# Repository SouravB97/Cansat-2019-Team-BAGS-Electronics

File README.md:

# Cansat-2019-Team-BAGS-Electronics
Technical resources pertaining to the cansat created by Team BAGS in June 2019

The cansat contains 3 independant systems.

Section A is responsible for the overall telemetry and processing. It is fitted into the payload and has several I/O devices, including the zigbee radio which communicates with the ground station.

Section B is the camera module. It contains the camera as well as the equipment needed to stabilise it, which ensures that the camera points to one direction with respect to the earth's magnetic field, even if the cansat overall rotates continuosly.

Section C is the container module. It houses the container while the cansat is in the rocket, and releases it at an altitude of 450m as specified in the mission guidelines.

The ground station is reponsible for receiving the telemetry data from the cansat. It uses this data to generate a csv file, sensor data graphs, gps plots, and a tilt animation of the deployed cansat.

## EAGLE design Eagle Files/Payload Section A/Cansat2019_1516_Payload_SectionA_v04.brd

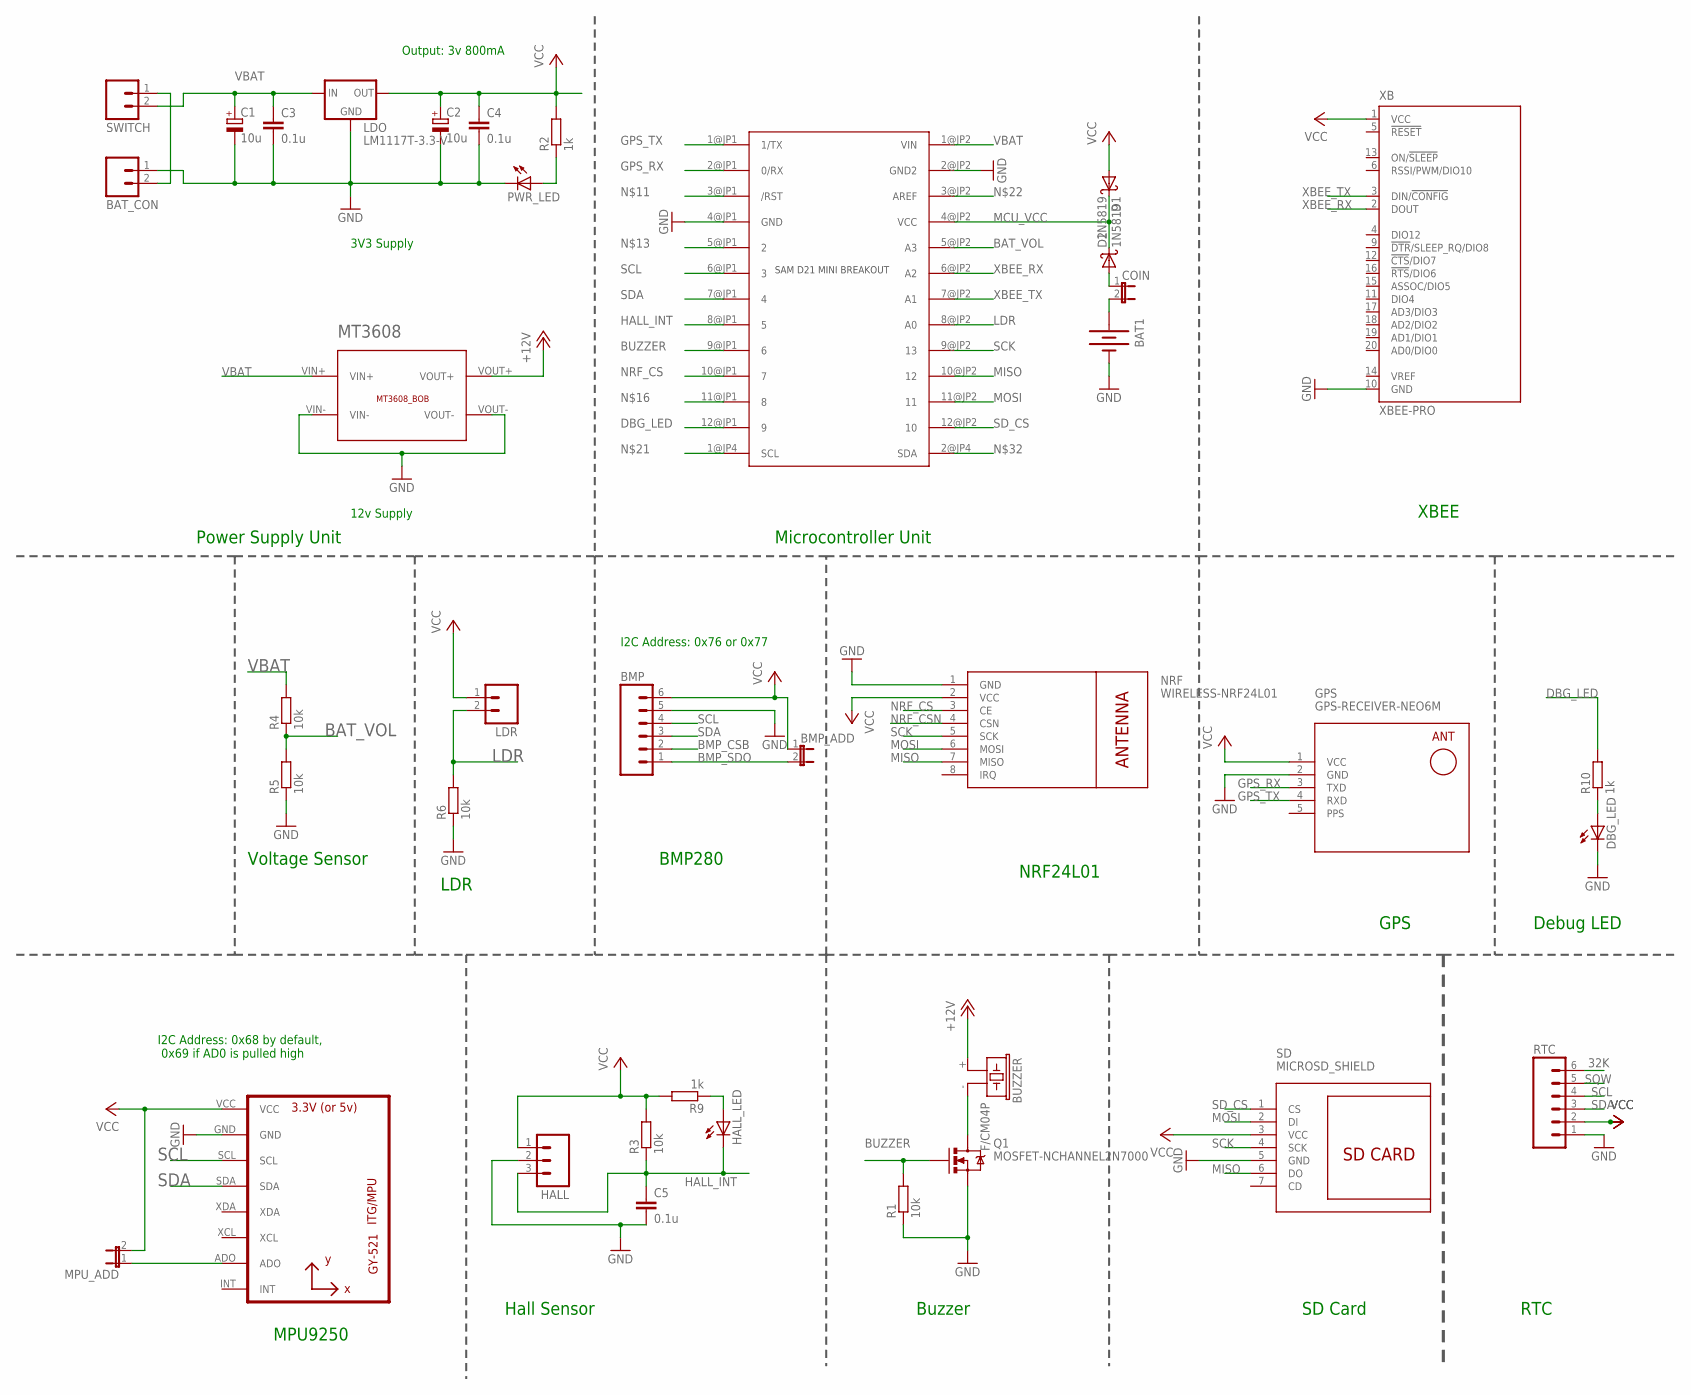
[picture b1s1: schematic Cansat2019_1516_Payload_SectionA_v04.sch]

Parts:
BAT1: BATTERY20PTH; BATTCOM_20MM_PTH
BAT_CON: M02; 02P
BMP: M06; 06P
BMP_ADD: JUMPER-2PTH; 1X02
BUZZER: F/CM04P
C1, C2: 10u; E2,5-6
C3, C4, C5: 0.1u; C025-025X050
COIN: JUMPER-2PTH; 1X02
D1, D2: 1N5819; DO41-10
DBG_LED: LED3MM
GPS: GPS-RECEIVER-NEO6M
HALL: M03; 03P
HALL_LED: LED3MM
LDO: LM1117T-3.3-V; TO220V
LDR: M02; 02P
MPU: GY-521MPU6050; GY-521
MPU_ADD: JUMPER-2PTH; 1X02
MT3608: MT3608_BOB
NRF: WIRELESS-NRF24L01
PWR_LED: LED3MM
Q1: MOSFET-NCHANNEL2N7000; TO-92
R1, R3, R4, R5, R6: 10k; 0204/7
R2, R9, R10: 1k; 0204/7
RTC: M06; 06P
SAMD: SAM_D21_MINI_BREAKOUT; JP1_SPARKFUN-SAMD21-MINI-BREAKOUT-V10
SD: MICROSD_SHIELD
SWITCH: M02; 02P
XB: XBEE-PRO

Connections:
32K: RTC.6
+12V: BUZZER.+ (1), MT3608.VOUT+
BAT_VOL: R4.1, R5.2, SAMD.5@JP2 (A3)
BMP_CSB: BMP.2
BMP_SDO: BMP.1, BMP_ADD.2
BUZZER: Q1.2 (G), R1.2, SAMD.9@JP1 (6)
DBG_LED: R10.2, SAMD.12@JP1 (9)
GND: BAT1.2 (-), BAT_CON.1, BMP.5, C1.-, C2.-, C3.2, C4.2, C5.2, DBG_LED.K (C), GPS.2 (GND), HALL.2, LDO.1 (GND), MPU.GND, MT3608.VIN-, MT3608.VOUT-, NRF.1 (GND), PWR_LED.K (C), Q1.1 (S), R1.1, R5.1, R6.1, RTC.1, SAMD.2@JP2 (GND2), SAMD.4@JP1 (GND), SD.5 (GND), XB.10 (GND)
GPS_RX: GPS.3 (TXD), SAMD.2@JP1 (0/RX)
GPS_TX: GPS.4 (RXD), SAMD.1@JP1 (1/TX)
HALL_INT: C5.1, HALL.3, HALL_LED.K (C), R3.1, SAMD.8@JP1 (5)
LDR: LDR.2, R6.2, SAMD.8@JP2 (A0)
MCU_VCC: D1.C, D2.C, SAMD.4@JP2 (VCC)
MISO: NRF.7 (MISO), SAMD.10@JP2 (12), SD.6 (DO)
MOSI: NRF.6 (MOSI), SAMD.11@JP2 (11), SD.2 (DI)
unnamed: BUZZER.- (2), Q1.3 (D)
unnamed: COIN.1, D2.A
unnamed: PWR_LED.A, R2.1
unnamed: BAT1.1 (+), COIN.2
unnamed: BAT_CON.2, SWITCH.1
unnamed: MPU.ADO, MPU_ADD.1
unnamed: HALL_LED.A, R9.1
unnamed: DBG_LED.A, R10.1
NRF_CS: NRF.3 (CE), SAMD.10@JP1 (7)
NRF_CSN: NRF.4 (CSN)
PPS: GPS.5 (PPS)
SCK: NRF.5 (SCK), SAMD.9@JP2 (13), SD.4 (SCK)
SCL: BMP.4, MPU.SCL, RTC.4, SAMD.6@JP1 (3)
SDA: BMP.3, MPU.SDA, RTC.3, SAMD.7@JP1 (4)
SD_CS: SAMD.12@JP2 (10), SD.1 (CS)
SQW: RTC.5
VBAT: C1.+, C3.1, LDO.3 (IN), MT3608.VIN+, R4.2, SAMD.1@JP2 (VIN), SWITCH.2
VCC: BMP.6, BMP_ADD.1, C2.+, C4.1, D1.A, GPS.1 (VCC), HALL.1, LDO.2 (OUT), LDR.1, MPU.VCC, MPU_ADD.2, NRF.2 (VCC), R2.2, R3.2, R9.2, RTC.2, SD.3 (VCC), XB.1 (VCC)
XBEE_RX: SAMD.6@JP2 (A2), XB.2 (DOUT)
XBEE_TX: SAMD.7@JP2 (A1), XB.3 (DIN/!CONFIG)

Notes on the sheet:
Power Supply Unit
3V3 Supply
12v Supply
Output: 3v 800mA
Microcontroller Unit
Buzzer
Voltage Sensor
BMP280
GPS
XBEE
MPU9250
SD Card
NRF24L01
LDR
Hall Sensor
I2C Address: 0x76 or 0x77
I2C Address: 0x68 by default, 0x69 if AD0 is pulled high
RTC
Debug LED

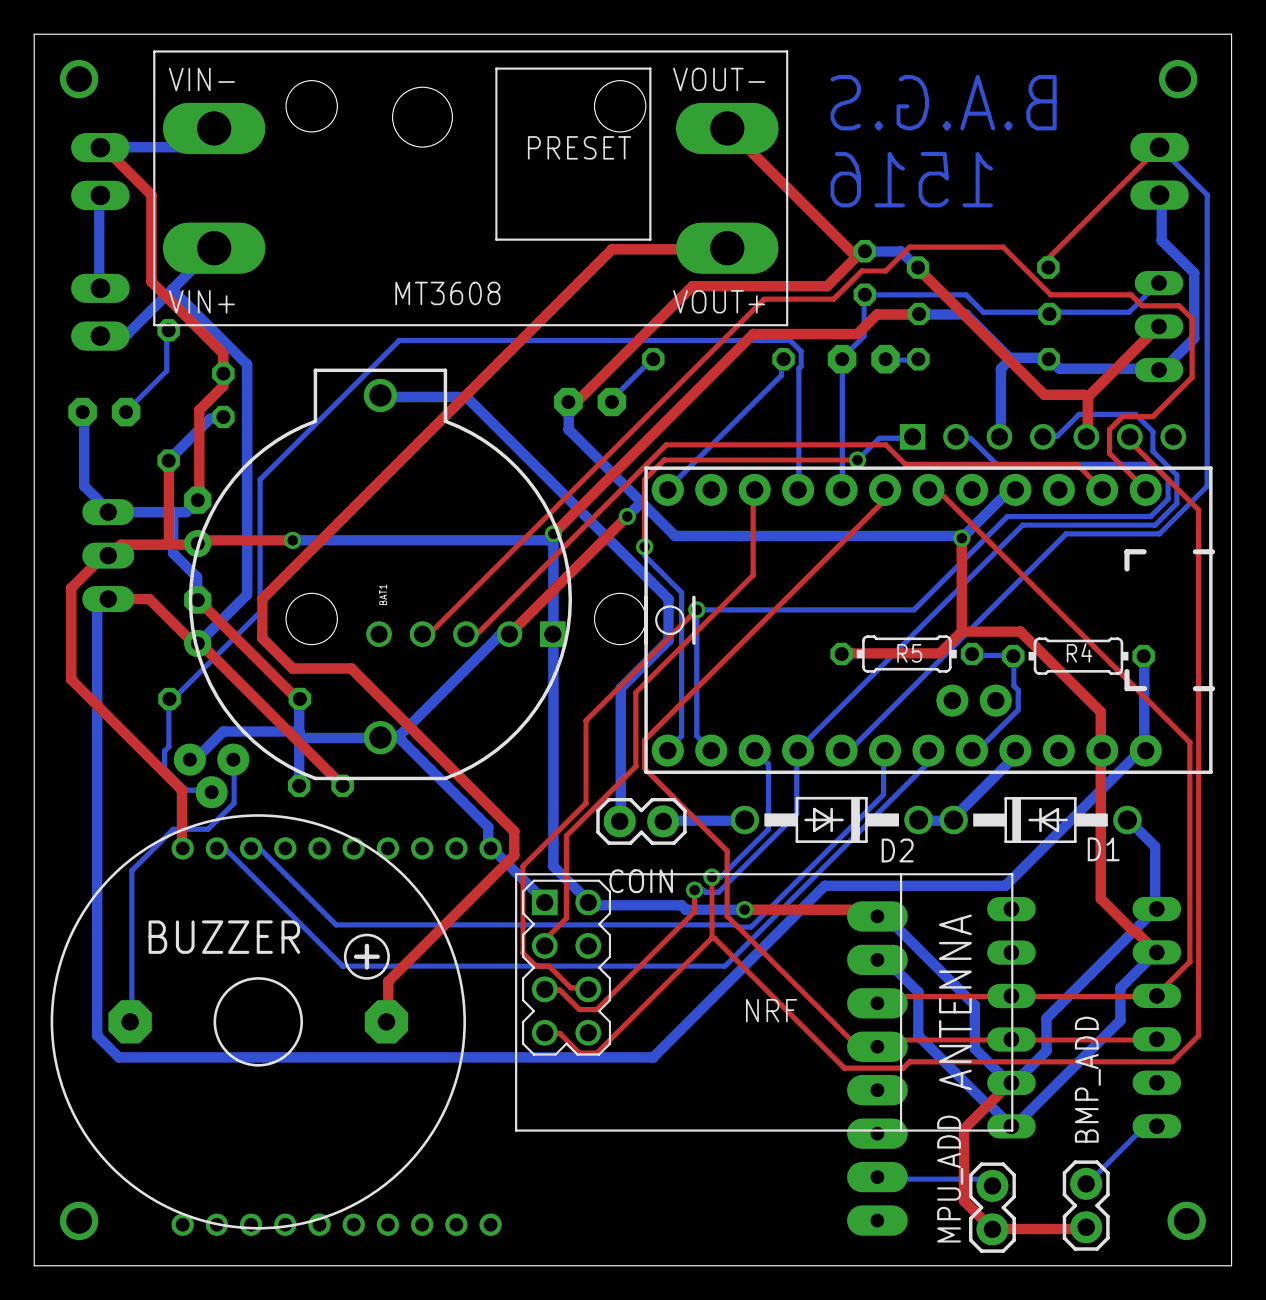
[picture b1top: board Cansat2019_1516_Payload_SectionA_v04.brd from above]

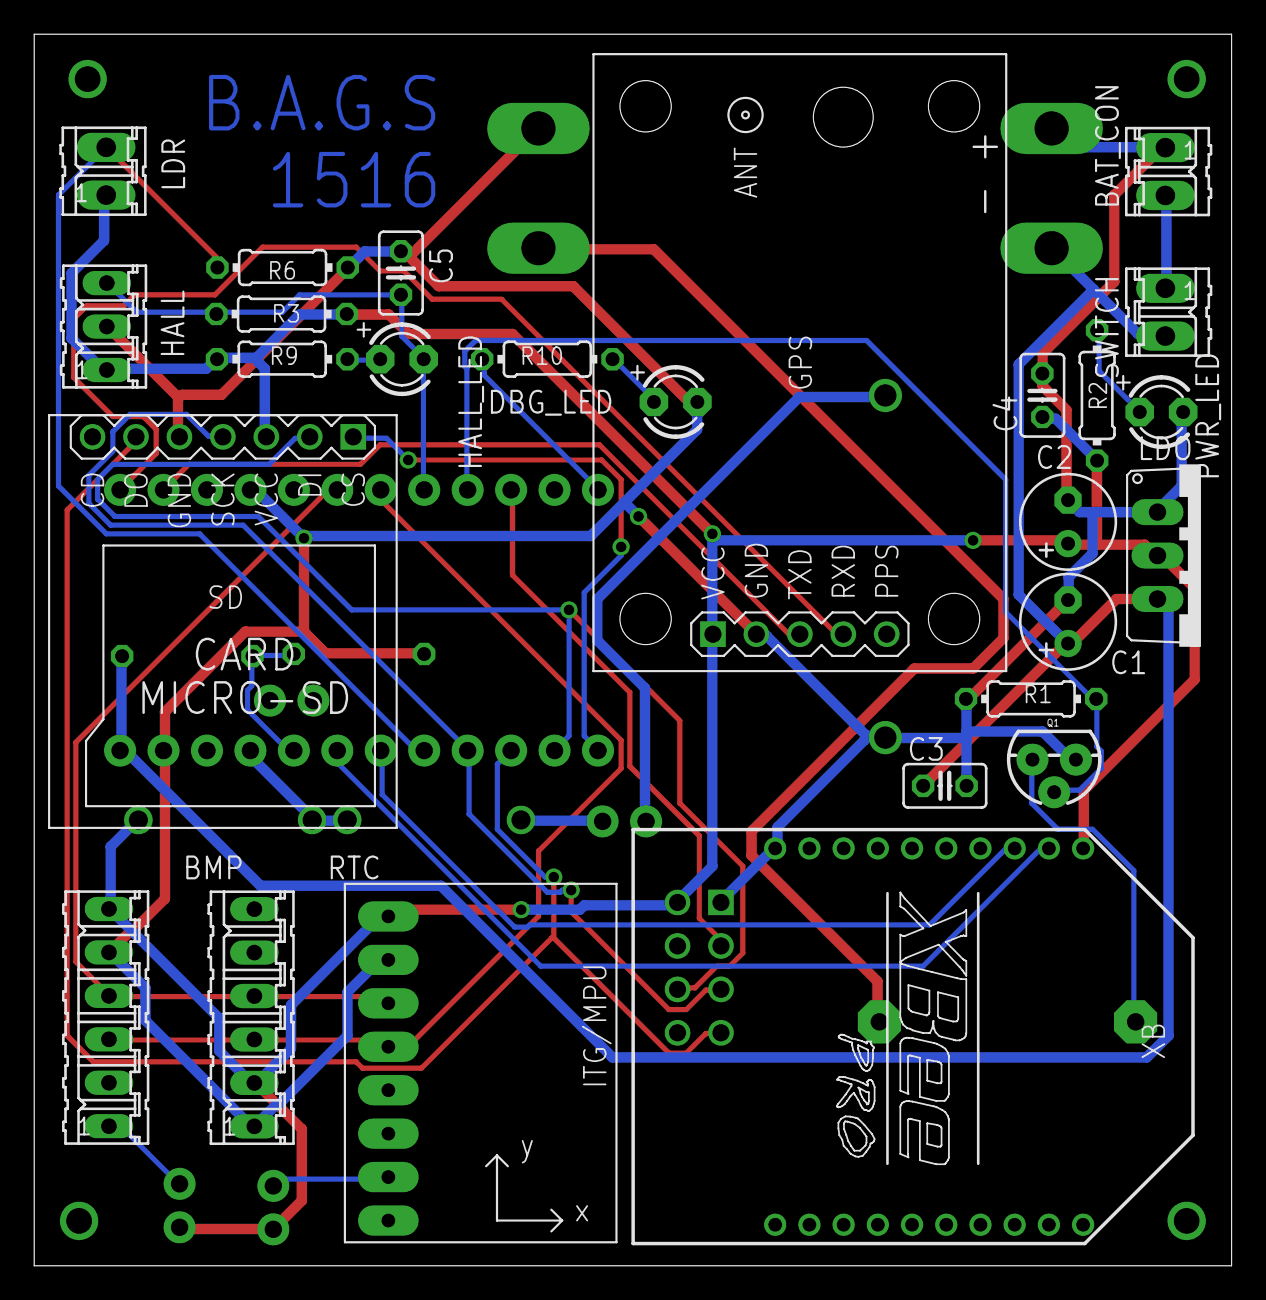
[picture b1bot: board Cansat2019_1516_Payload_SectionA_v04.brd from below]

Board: 2 copper layers, 70.0 x 72.0 mm, 38 parts (26 on the bottom side), 30 nets.

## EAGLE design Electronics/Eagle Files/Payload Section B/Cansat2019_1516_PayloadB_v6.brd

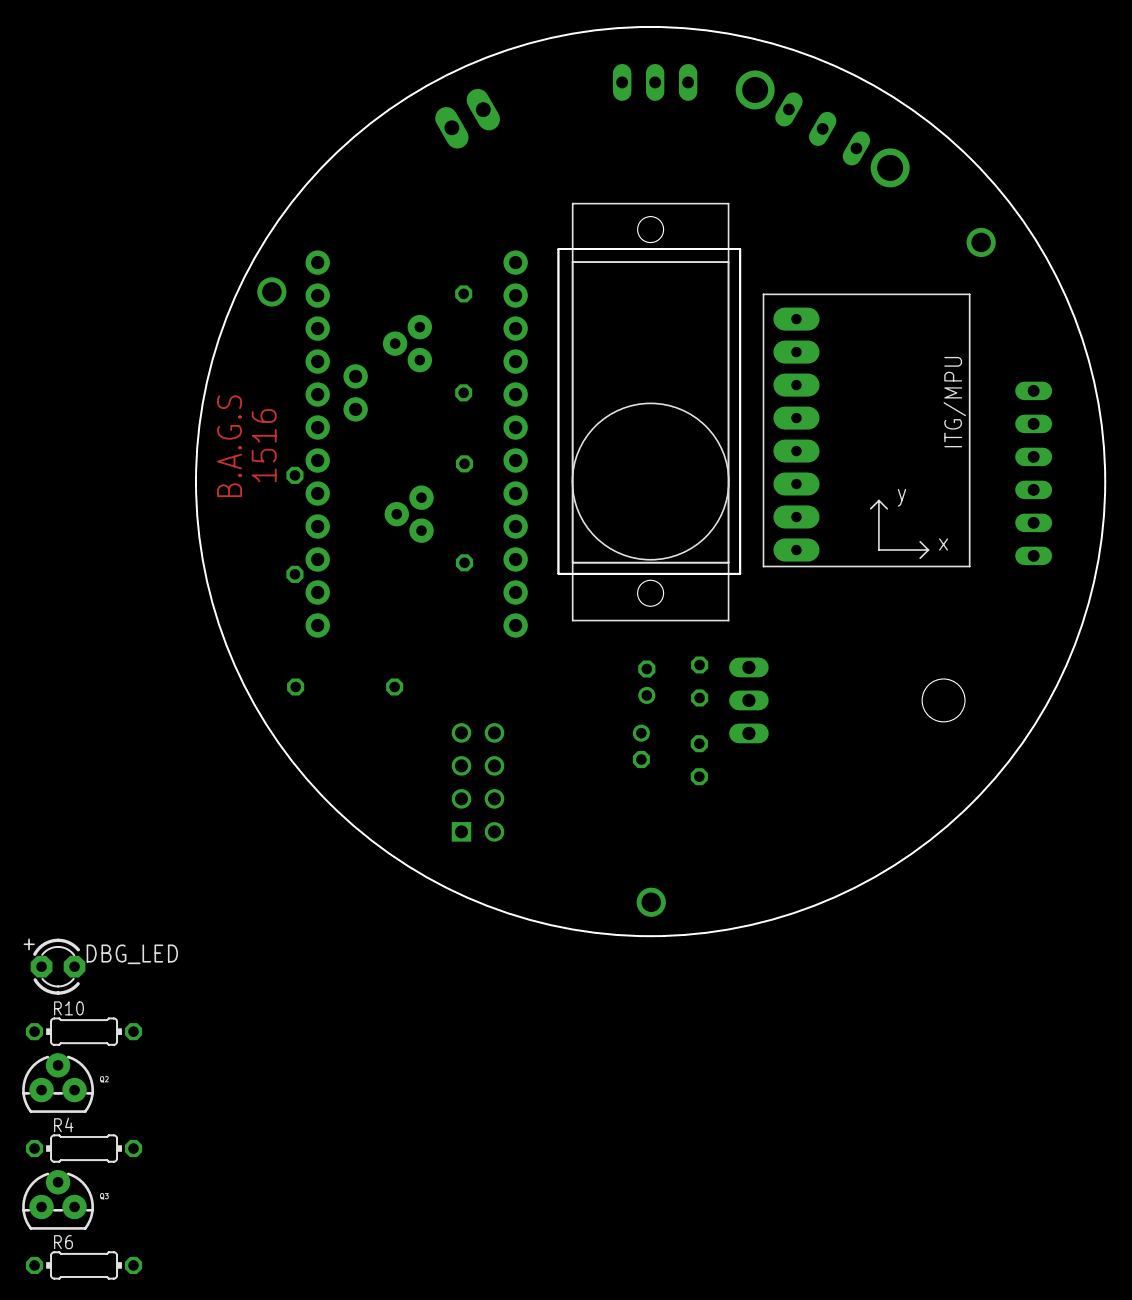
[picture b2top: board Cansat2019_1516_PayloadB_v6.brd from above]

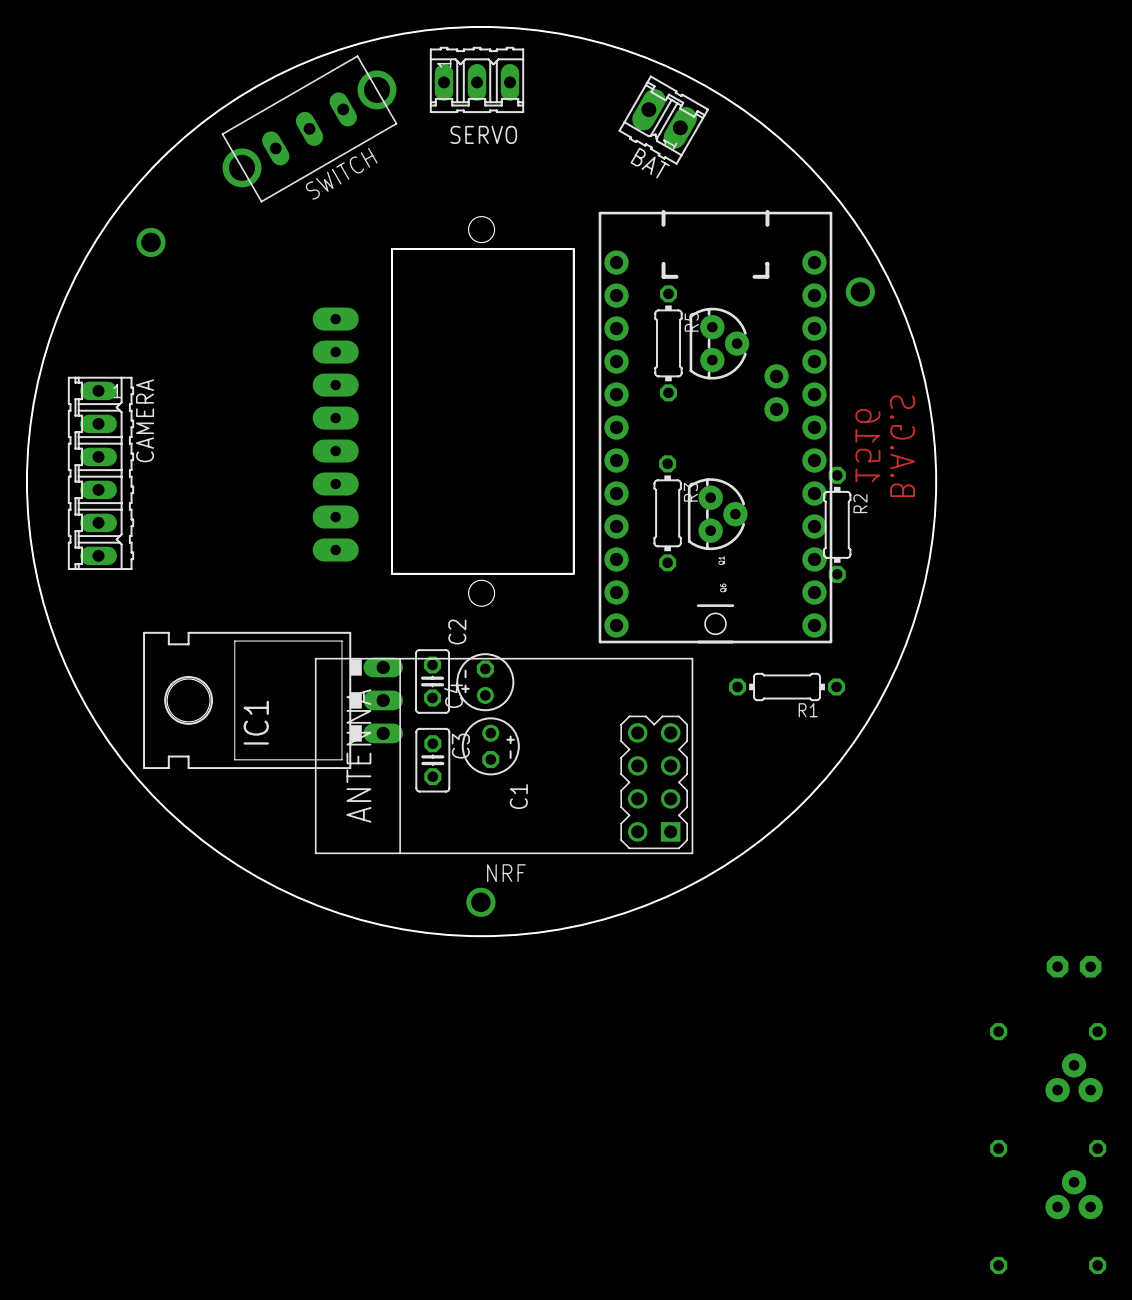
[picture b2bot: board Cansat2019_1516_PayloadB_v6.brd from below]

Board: 2 copper layers, 70.0 x 70.0 mm, 25 parts (17 on the bottom side), 23 nets, no tracks yet.

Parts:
BAT: 02P
C1, C2: 10u; E2-4
C3, C4: 0.1u; C025-025X050
CAMERA: 06P
DBG_LED: LED3MM
IC1: TO-220-ALT
MPU: GY-521MPU6050; GY-521
NRF: WIRELESS-NRF24L01
Q1, Q2, Q3, Q6: MOSFET-NCHANNEL2N7000; TO-92
R1, R2, R3, R4, R5, R6: 10k; 0204/7
R10: 1k; 0204/7
SERVO: 03P
SWITCH: SLIDESWITCH-BIG; BIGSWITCH
U$1: SG90_TOP
U$2: JP1_SPARKFUN-SAMD21-MINI-BREAKOUT-V10

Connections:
!POWER: Q3.2, R6.2
BAT_VOL: R1.1, R2.2, U$2.8@JP2
CE: NRF.3, U$2.11@JP1
CSN: NRF.4, U$2.12@JP2
DBG_LED: R10.2, U$2.12@JP1
GND: BAT.1, C1.-, C2.-, C3.2, C4.2, CAMERA.6, DBG_LED.K, IC1.GND, MPU.GND, NRF.1, Q3.1, Q6.1, R2.1, R3.1, R5.1, R6.1, SERVO.1, U$2.2@JP2, U$2.4@JP1
MISO: NRF.7, U$2.10@JP2
MODE: Q6.2, R5.2, U$2.9@JP1
MODE_O: CAMERA.4, Q6.3
MOSI: NRF.6, U$2.11@JP2
unnamed: BAT.2, SWITCH.3
unnamed: Q2.2, Q3.3, R4.1
unnamed: DBG_LED.A, R10.1
POWER: Q1.2, R3.2, U$2.8@JP1
POWER_OH: CAMERA.2, Q1.3, Q2.3
POWER_OL: CAMERA.3, Q1.1, Q2.1
SCK: NRF.5, U$2.9@JP2
SCL: MPU.SCL, U$2.6@JP1
SDA: MPU.SDA, U$2.7@JP1
SERVO: SERVO.3, U$2.10@JP1
V5: C2.+, C4.1, CAMERA.1, IC1.OUT, R4.2, SERVO.2, U$2.1@JP2
V33: MPU.ADO, MPU.VCC, NRF.2, U$2.4@JP2
VBAT: C1.+, C3.1, IC1.IN, R1.2, SWITCH.1, SWITCH.2

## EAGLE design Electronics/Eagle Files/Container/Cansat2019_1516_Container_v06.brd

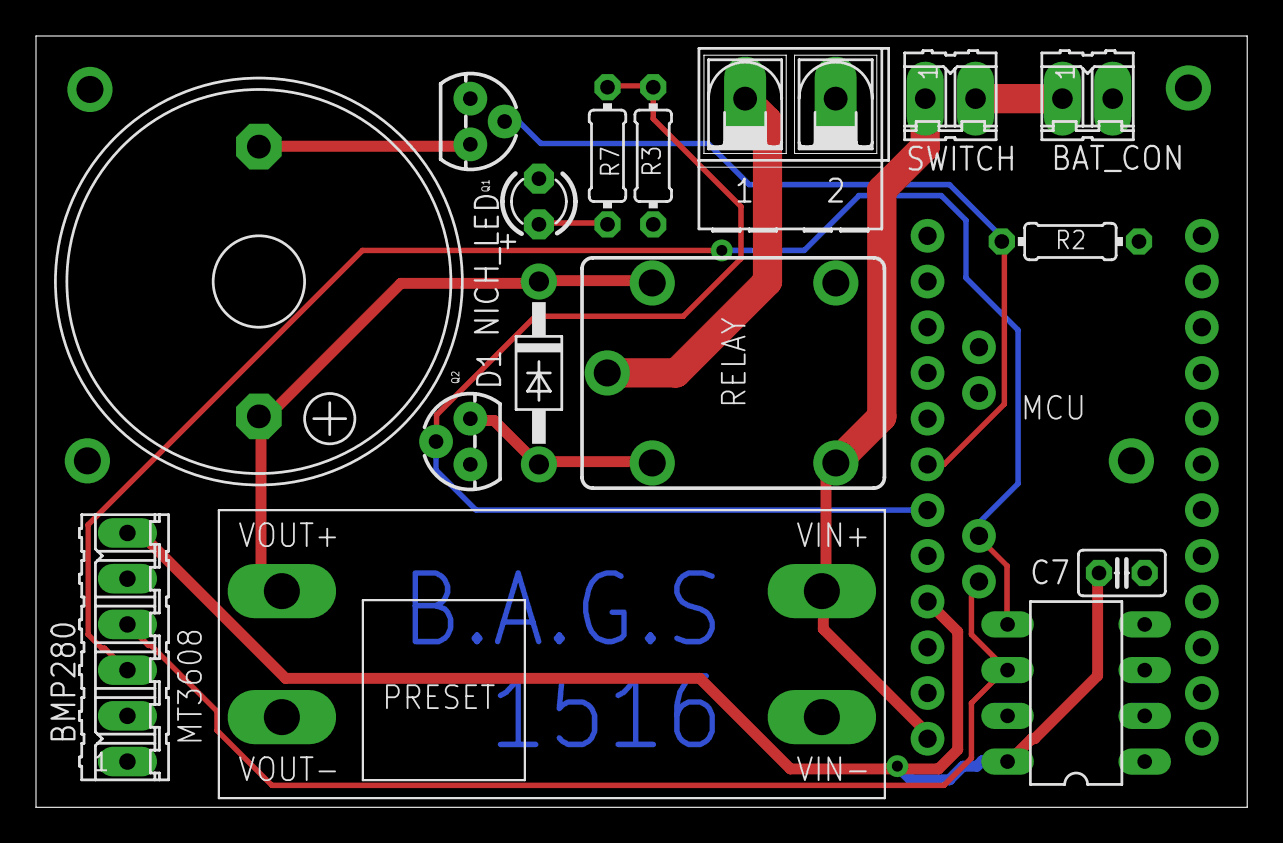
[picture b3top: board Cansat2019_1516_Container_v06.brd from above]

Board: 2 copper layers, 67.3 x 42.9 mm, 17 parts (0 on the bottom side), 13 nets.

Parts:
BAT_CON: 02P
BMP280: 06P
BUZZER: EB2209A
C7: 0.1u; C025-025X050
D1: 1N4004; DO41-10
EEPROM: 24AA64P; DIL8
MCU: ARDUINO_PRO_MINI
MT3608: MT3608_BOB
NICHROME_WIRE: AK500/2-H
NICH_LED: LED3MM
Q1, Q2: MOSFET-NCHANNEL2N7000; TO-92
R2, R3: 10k; 0204/7
R7: 1k; 0204/7
RELAY: CQ1-12V; CQ1
SWITCH: 02P

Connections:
+12V: BUZZER.+, D1.C, MT3608.VOUT+, RELAY.1
BUZZER: MCU.18, Q1.2, R2.2
GND: BAT_CON.2, BMP280.5, C7.2, EEPROM.1, EEPROM.2, EEPROM.3, EEPROM.4, MCU.4, MCU.23, MT3608.VIN-, MT3608.VOUT-, NICHROME_WIRE.2, NICH_LED.K, Q1.1, Q2.1, R2.1, R3.2
unnamed: BUZZER.-, Q1.3
unnamed: NICHROME_WIRE.1, RELAY.C
unnamed: NICH_LED.A, R7.1
unnamed: BAT_CON.1, SWITCH.2
unnamed: D1.A, Q2.3, RELAY.2
NCH_WIR: MCU.19, Q2.2, R3.1, R7.2
SCL: BMP280.4, EEPROM.6, MCU.A5
SDA: BMP280.3, EEPROM.5, MCU.A4
VBAT: MCU.24, MT3608.VIN+, RELAY.NO, SWITCH.1
VCC: BMP280.6, C7.1, EEPROM.8, MCU.21

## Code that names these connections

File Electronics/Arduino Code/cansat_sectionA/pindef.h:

#include <Arduino.h>   // required before wiring_private.h
#include <Wire.h>
#include <SPI.h>
#include <SD.h>
#include <RTCZero.h>
#include <MadgwickAHRS.h>
#include <TinyGPS++.h>
#include <RH_NRF24.h>

#include "wiring_private.h" // pinPeripheral() function
#include "Adafruit_BMP280.h"
#include "MPU6050_tockn.h"
#include "packet.h"

#define UART0_RX 0	//defined by default Serial1
#define UART0_TX 1

#define UART1_RX A2 //Serial2
#define UART1_TX A1

#define SDA 4 //Wire1
#define SCL 3

#define MOSI 11 //default SPI
#define MISO 12
#define SCK  13

#define NRF_CE			8		//NRF only works with these pins.
#define NRF_CSN			10	//So they are hardwired. This is just for the programmer.

#define BAT_VOL			A3
#define HALL_INT		5
#define SD_SELECT		7
#define POW_WAKEUP	A3	//8
#define LDR 				A0
#define BUZZER			6
#define DBG_LED			9

#define Serial			SerialUSB
#define gps_uart		Serial1
#define zigbee			Serial2

#define LOG_MISSION			//enable this to log mission events to SD card
#define SER_DEBUG				//enable this to get debug info in serial monitor
#define TEAM_ID 1516		//BAGS

#define BOOT				0		//reset
#define INIT				1		//Sensors initialised and ready for telemetry
#define TELEMETRY		2		//performing telemetry and related computation
#define RECOVERY		3		//waiting for recovery from crew

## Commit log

2019-06-06 Added all the files.
2019-06-06 Added GCS Software folder

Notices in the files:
parts and their libraries:
SparkFun-Retired: Licensing:Creative Commons ShareAlike 4.0 International - https://creativecommons.org/licenses/by-sa/4.0
diy-modules: Released under the Creative Commons Attribution 4.0 International License: http://creativecommons.org/licenses/by/4.0
